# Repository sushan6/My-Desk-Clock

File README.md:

# My Desk Clock

I'm building a custom desk clock using an ESP32. The idea is to make a clock that automatically synchronises its time over Wi-Fi, so there's no need to set the time manually.

I designed the circuit schematic and PCB in KiCad and am also working on a custom 3D-printed enclosure. The clock uses an ESP32 for Wi-Fi connectivity and a dedicated RTC for timekeeping.

## Features

- ESP32-WROOM-32E microcontroller
- Automatic time synchronisation over Wi-Fi using NTP
- DS3231M real-time clock
- Rechargeable battery-based power supply
- USB-C charging and power input
- Custom PCB designed in KiCad
- Five tactile push buttons
- Passive buzzer
- Custom 3D-printed enclosure

# 3D Model

This is the 3D model of the clock enclosure. I designed it around the PCB so that all the components fit inside without making the clock unnecessarily bulky.

# 3D Render

Here's the 3D render of the clock. It gives a better idea of how the finished enclosure is supposed to look.

# Physical PCB Layout

The PCB was designed in KiCad. I arranged the components around the ESP32, RTC, and power management circuit while keeping the board compact enough to fit inside the enclosure.

# Circuit Schematic

The schematic shows how the different sections of the clock connect together, including the ESP32, RTC, battery charging circuit, buck-boost converter, buttons, and buzzer.

# How It Works

The ESP32 is the main controller of the clock. It connects to a Wi-Fi network and retrieves the current time from an NTP server.

The DS3231M RTC provides independent timekeeping, allowing the clock to keep track of time even when Wi-Fi isn't available. The ESP32 can synchronise the RTC when an internet connection is available.

The five tactile buttons are intended for physical controls, while the buzzer can be used for sound alerts.

## Power Management

I designed the power circuit around a rechargeable battery.

- **BQ24074:** Handles battery charging and power management.
- **TPS63031:** Provides regulated power using a buck-boost converter.
- **USB-C connector:** Provides the charging and power input.

The idea is to have a clock that can run without needing to stay connected to a USB cable all the time.

# Design Files

The project includes the KiCad schematic, PCB layout, and 3D enclosure model.

These files can be used to inspect the circuit, modify the PCB, or manufacture your own version of the clock.

# Acknowledgements

This project was designed using **KiCad EDA**. Thanks to the KiCad developers and the open-source hardware community for making PCB design tools accessible.

---

# License

This project is open-source. Feel free to inspect, modify, and build upon the design.

---

# Bill of Materials (BOM)

The following table contains the components used in the clock, along with their quantities, supplier links, and estimated prices.

## Main BOM

| **Item** | **Link** | **Quantity** | **Cost (USD)** | **Notes** |
|---|---|---:|---:|---|
| CR2032 battery holder | [Lion Circuits](https://www.lioncircuits.com/parts/1057) | 1 | $2.11 | Keystone 1057 |
| Passive buzzer | [Robu.in](https://robu.in/product/ac1470-cldz-piezoelectric-passive-buzzer-1-25v14x7mm/) | 1 | $0.09 | 12 × 9.5 mm footprint |
| 100 nF capacitors | [Robu.in](https://robu.in/product/100nf-0805-surface-mount-multilayer-ceramic-capacitor-pack-of-40/) | 3 | $0.03 | 0805 |
| 10 µF capacitors | [Robu.in](https://robu.in/product/0805x106k250nt-fh-25v-10uf-x5r%C2%B110-0805-multilayer-ceramic-capacitors-mlcc-smd-smt-rohs/) | 6 | $0.31 | 0805 |
| 1 µF capacitors | [Robu.in](https://robu.in/product/1uf-1000nf-50v-capacitor-0805-smd-package-pack-of-10/) | 2 | $0.03 | 0805 |
| 4.7 µF capacitor | [Robu.in](https://robu.in/product/20121h475k125ab-tdk-ap-smd-ml-4-7-%c2%b5f-50-v-0805-pack-of-1/) | 1 | $0.15 | 0805 |
| 1×6 pin header | [Robu.in](https://robu.in/product/2-54mm-1x40-pin-male-single-row-straight-short-header-strip-pack-of-3/) | 1 | $0.10 | 2.54 mm |
| 1×4 pin header | [Robu.in](https://robu.in/product/2-54mm-1x40-pin-male-single-row-straight-short-header-strip-pack-of-3/) | 1 | $0.10 | 2.54 mm |
| USB-C receptacle | [Robu.in](https://robu.in/product/u262-161n-4bs165-xkb-5a-1-16p-female-type-c-smd-usb-connectors-rohs/) | 1 | $0.33 | 16-pin |
| JST PH 2-pin connector | [Robu.in](https://robu.in/product/wafer-xh2-54-2pzz-xunpu-1x2p-xh-2p/) | 1 | $0.00 | Verify connector type and price |
| 1.5 µH inductor | [Robu.in](https://robu.in/product/dfe252012p-1r5mp2-murata-power-inductor-smd-1-5-%c2%b5h-shielded-3-a1008-2520-metric/) | 1 | $0.03 | SMD |
| NPN transistor | [Robu.in](https://robu.in/product/s8050-kuu-25v-300mw-500ma-npn-sot-23-bipolar-bjt-rohs/) | 1 | $0.01 | SOT-23 |
| 10 kΩ resistors | [Robu.in](https://robu.in/product/rc0805jr-0710kl-yageo-smd-chip-resistor-10-kohm-pack-of-10/) | 3 | $0.01 | 0805 |
| 4.7 kΩ resistors | [Robu.in](https://robu.in/product/crcw08054k70fkeac-vishay-intertech-4-7k-0805-chip-resistor/) | 3 | $0.02 | 0805 |
| 100 kΩ resistors | [Robu.in](https://robu.in/product/rc0805fr-13100kl-yageo-smd-chip-resistor-100-kohm/) | 2 | $0.02 | 0805 |
| 1 kΩ resistor | [Robu.in](https://robu.in/product/1k-ohm-1-4w-0805-surface-mount-chip-resistor-pack-of-10/) | 1 | $0.00 | 0805 |
| 5.1 kΩ resistors | [Robu.in](https://robu.in/product/era6aeb102vpanasonicsmd-chip-resistor-1-kohm/) | 2 | $0.08 | Verify listing value |
| 1.78 kΩ resistor | [Mouser India](https://www.mouser.in/en/ProductDetail/Panasonic-Industry/ERJ-P06F1781V) | 1 | $0.23 | SMD |
| 3 kΩ resistor | [Robu.in](https://robu.in/product/rc0805fr-073kl-yageo-res-thick-film-0805-3k-ohm/) | 1 | $0.00 | 0805 |
| Tactile push buttons | [Robu.in](https://robu.in/product/6x6x5mm-tactile-push-button-switch-pack-of-20/) | 5 | $0.09 | 6 × 6 mm |
| ESP32-WROOM-32E | [Robu.in](https://robu.in/product/espressif-esp32-wroom-32-4m-32mbit-flash-wifi-bluetooth-module/) | 1 | $3.21 | Main controller |
| DS3231M RTC | [Robu.in](https://robu.in/product/ds3231mtrl-analog-devices-real-time-clock-ic/) | 1 | $3.84 | Real-time clock |
| BQ24074 charger IC | [Robu.in](https://robu.in/product/bq24075rgtt-texas-instruments-vqfn-16-ep3x3-battery-management-rohs/) | 1 | $1.92 | Verify exact part number |
| TPS63031 buck-boost IC | [Robu.in](https://robu.in/product/tps63031dskr-texas-instruments-buck-boost-switching-regulator-ic/) | 1 | $1.90 | Power regulation |

## Cost Summary

| **Item** | **Cost (USD)** |
|---|---:|
| Components | $14.60 |
| PCB | $12.00 |
| **Total estimated cost** | **$26.60** |

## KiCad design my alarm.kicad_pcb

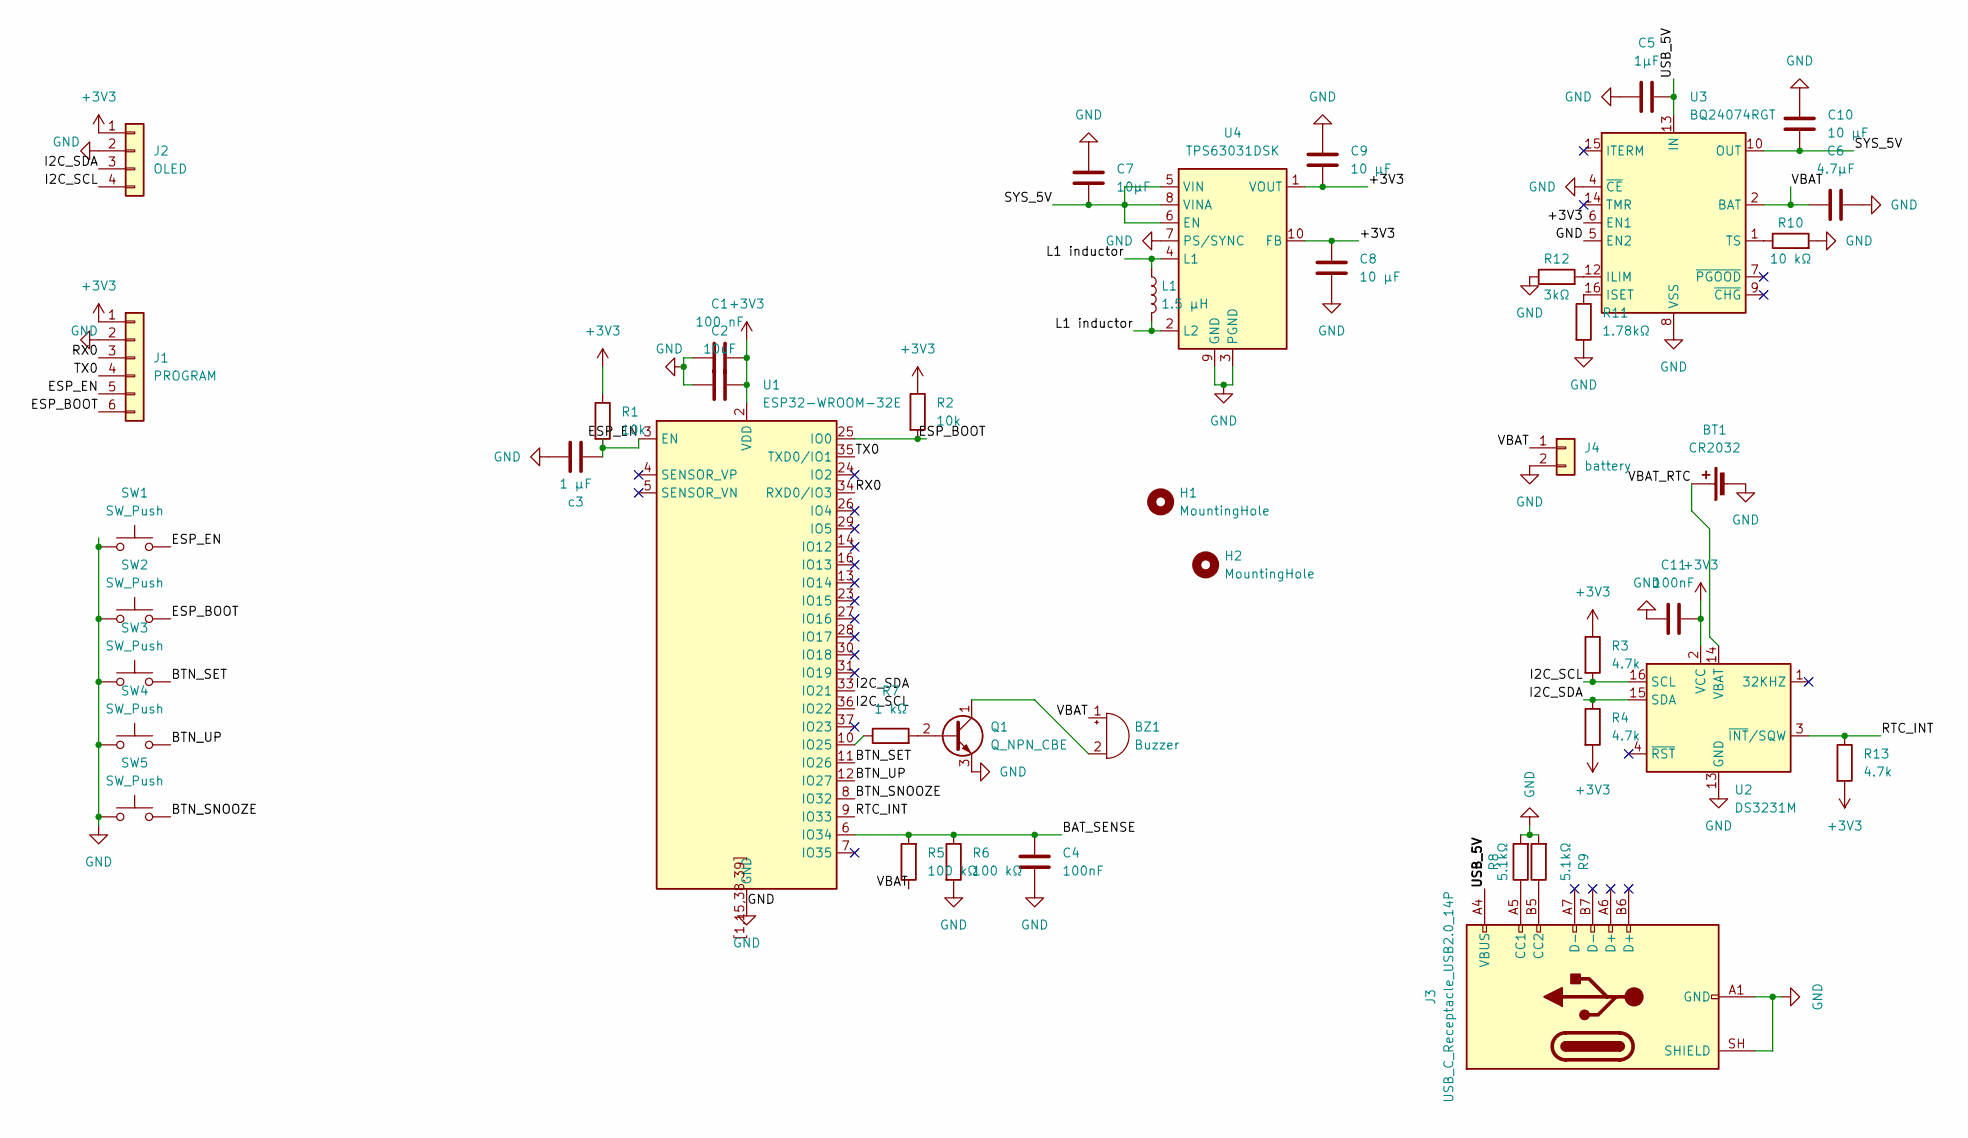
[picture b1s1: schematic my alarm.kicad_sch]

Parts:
BT1: CR2032; BatteryHolder_Keystone_1057_1x2032
BZ1: Buzzer; Buzzer_12x9.5RM7.6
C1: 100 nF; C_0805_2012Metric
C2: 10uF; C_0805_2012Metric
C4, C11: 100nF; C_0805_2012Metric
C5: 1µF; C_0805_2012Metric
C6: 4.7µF; C_0805_2012Metric
C7: 10µF; C_0805_2012Metric
C8, C9, C10: 10 µF; C_0805_2012Metric
H1, H2: MountingHole; MountingHole_2.1mm
J1: PROGRAM; PinHeader_1x06_P2.54mm_Vertical
J2: OLED; PinHeader_1x04_P2.54mm_Vertical
J3: USB_C_Receptacle_USB2.0_14P; USB_C_Receptacle_GCT_USB4105-xx-A_16P_TopMnt_Horizontal
J4: battery; JST_PH_S2B-PH-K_1x02_P2.00mm_Horizontal
L1: 1.5 µH; L_1008_2520Metric_Pad1.43x2.20mm_HandSolder
Q1: Q_NPN_CBE; SOT-23
R1, R2: 10k; R_0805_2012Metric
R3, R4, R13: 4.7k; R_0805_2012Metric
R5, R6: 100 kΩ; R_0805_2012Metric
R7: 1 kΩ; R_0805_2012Metric
R8, R9: 5.1kΩ; R_0805_2012Metric
R10: 10 kΩ; R_0805_2012Metric
R11: 1.78kΩ; R_0805_2012Metric
R12: 3kΩ; R_0805_2012Metric
SW1, SW2, SW3, SW4, SW5: SW_Push; SW_PUSH_6mm
U1: ESP32-WROOM-32E
U2: DS3231M; SOIC-16W_7.5x10.3mm_P1.27mm
U3: BQ24074RGT; VQFN-16-1EP_3x3mm_P0.5mm_EP1.6x1.6mm
U4: TPS63031DSK; WSON-10-1EP_2.5x2.5mm_P0.5mm_EP1.2x2mm
c3: 1 µF; C_0805_2012Metric

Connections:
+3V3: C1.2, C2.2, C8.1, C9.2, C11.1, J1.1, J2.1, R1.1, R2.1, R3.1, R4.2, R13.2, U1.2 (VDD), U2.2 (VCC), U3.6 (EN1), U4.1 (VOUT), U4.10 (FB)
/BAT_SENSE: C4.1, R5.2, R6.1, U1.6 (IO34)
/BTN_SET: SW3.2, U1.11 (IO26)
/BTN_SNOOZE: SW5.2, U1.8 (IO32)
/BTN_UP: SW4.2, U1.12 (IO27)
/ESP_BOOT: J1.6, R2.2, SW2.2, U1.25 (IO0)
/ESP_EN: J1.5, R1.2, SW1.2, U1.3 (EN), c3.2
/I2C_SCL: J2.4, R3.2, U1.36 (IO22), U2.16 (SCL)
/I2C_SDA: J2.3, R4.1, U1.33 (IO21), U2.15 (SDA)
/L1 inductor: L1.1, L1.2, U4.2 (L2), U4.4 (L1)
/RTC_INT: R13.1, U1.9 (IO33), U2.3 (~INT/SQW)
/RX0: J1.3, U1.34 (RXD0/IO3)
/SYS_5V: C7.2, C10.2, U3.10 (OUT), U3.11 (OUT), U4.5 (VIN), U4.6 (EN), U4.8 (VINA)
/TX0: J1.4, U1.35 (TXD0/IO1)
/USB_5V: C5.2, J3.A4 (VBUS), J3.A9 (VBUS), J3.B4 (VBUS), J3.B9 (VBUS), U3.13 (IN)
/VBAT: BZ1.1 (+), C6.1, J4.1, R5.1, U3.2 (BAT), U3.3 (BAT)
/VBAT_RTC: BT1.1 (+), U2.14 (VBAT)
GND: BT1.2 (-), C1.1, C2.1, C4.2, C5.1, C6.2, C7.1, C8.2, C9.1, C10.1, C11.2, J1.2, J2.2, J3.A1 (GND), J3.A12 (GND), J3.B1 (GND), J3.B12 (GND), J3.SH (SHIELD), J4.2, Q1.3 (E), R6.2, R8.2, R9.2, R10.2, R11.2, R12.1, SW1.1, SW2.1, SW3.1, SW4.1, SW5.1, U1.1 (GND), U1.15 (GND), U1.38 (GND), U1.39 (GND), U1.[1,15,38,39] (GND), U2.5 (GND), U2.6 (GND), U2.7 (GND), U2.8 (GND), U2.9 (GND), U2.10 (GND), U2.11 (GND), U2.12 (GND), U2.13 (GND), U3.4 (~CE), U3.5 (EN2), U3.8 (VSS), U3.17 (VSS), U4.3 (PGND), U4.7 (PS/SYNC), U4.9 (GND), U4.11 (PGND), c3.1
unnamed: BZ1.2 (-), Q1.1 (C)
unnamed: J3.A5 (CC1), R8.1
unnamed: J3.B5 (CC2), R9.1
unnamed: Q1.2 (B), R7.2
unnamed: R7.1, U1.10 (IO25)
unnamed: R12.2, U3.12 (ILIM)
unnamed: R11.1, U3.16 (ISET)
unnamed: R10.1, U3.1 (TS)

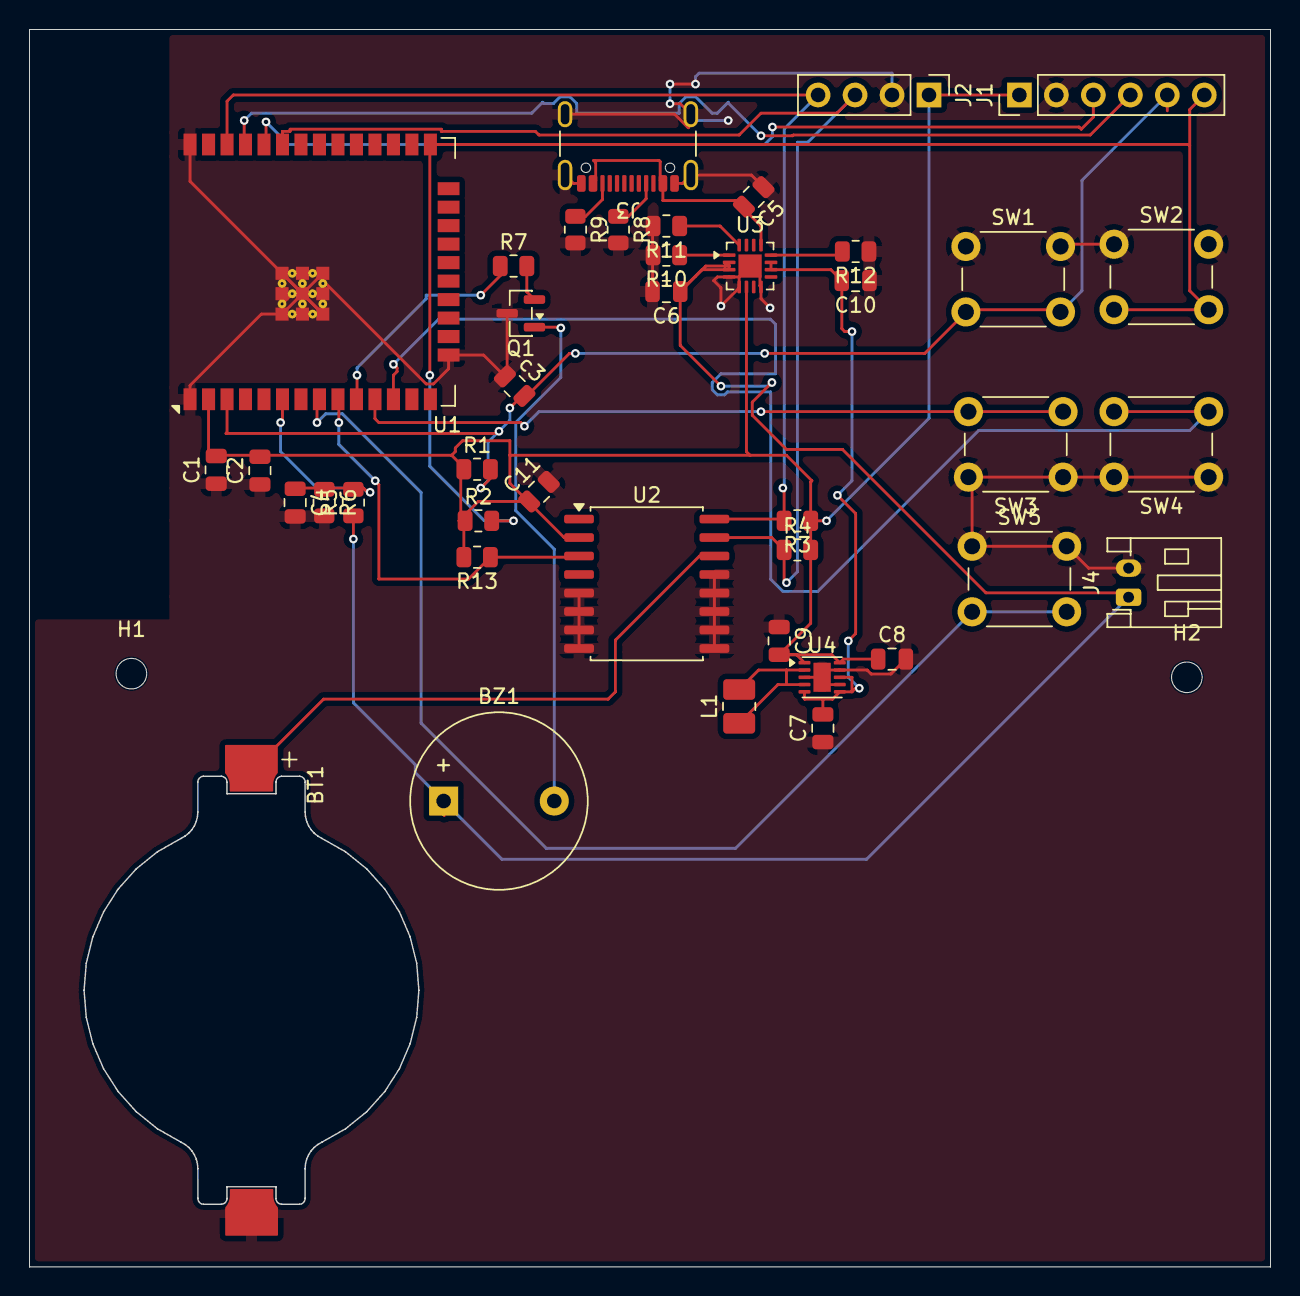
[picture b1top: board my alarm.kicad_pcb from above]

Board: 2 copper layers, 85.2 x 84.9 mm, 43 parts (0 on the bottom side), 26 nets.

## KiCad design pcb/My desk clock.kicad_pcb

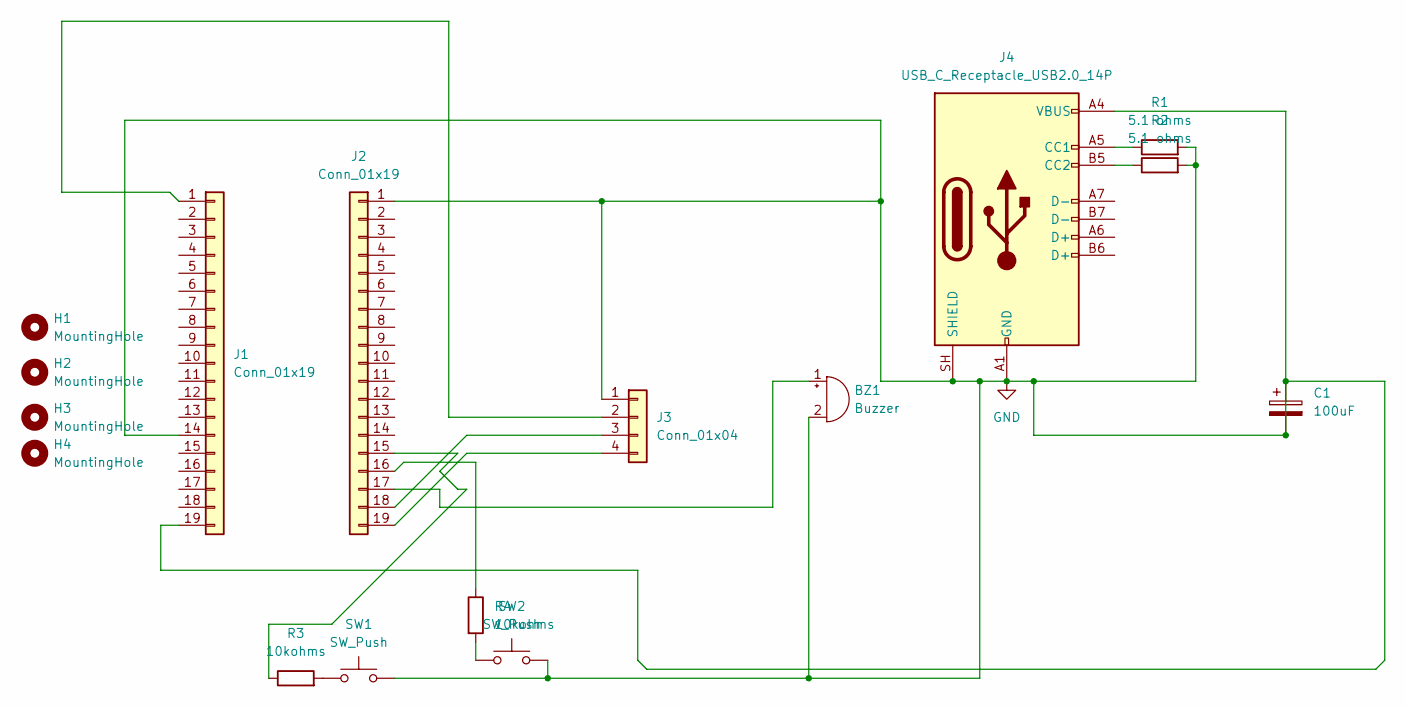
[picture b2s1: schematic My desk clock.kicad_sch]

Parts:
BZ1: Buzzer; Buzzer_Mallory_AST1240MLQ
C1: 100uF; DX_5R5VxxxxU_D11.5mm_P5.00mm
H1, H2, H3, H4: MountingHole; MountingHole_3.2mm_M3
J1, J2: Conn_01x19; PinSocket_1x19_P2.54mm_Vertical
J3: Conn_01x04; PinSocket_1x04_P2.54mm_Vertical
J4: USB_C_Receptacle_USB2.0_14P; USB_C_Receptacle_HRO_TYPE-C-31-M-12
R1, R2: 5.1 ohms; R_0805_2012Metric
R3, R4: 10kohms; R_0805_2012Metric
SW1, SW2: SW_Push; SW_PUSH_6mm

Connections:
GND: BZ1.2 (-), C1.1, C1.2, J1.14, J1.19, J2.1, J3.1, J4.A1 (GND), J4.A4 (VBUS), J4.A9 (VBUS), J4.A12 (GND), J4.B1 (GND), J4.B4 (VBUS), J4.B9 (VBUS), J4.B12 (GND), J4.SH (SHIELD), R1.2, R2.2, SW1.2, SW2.2
unnamed: BZ1.1 (+), J2.17
unnamed: J1.1, J3.2
unnamed: J2.15, R3.1
unnamed: J2.16, R4.1
unnamed: J2.18, J3.3
unnamed: J2.19, J3.4
unnamed: J4.A5 (CC1), R1.1
unnamed: J4.B5 (CC2), R2.1
unnamed: R3.2, SW1.1
unnamed: R4.2, SW2.1

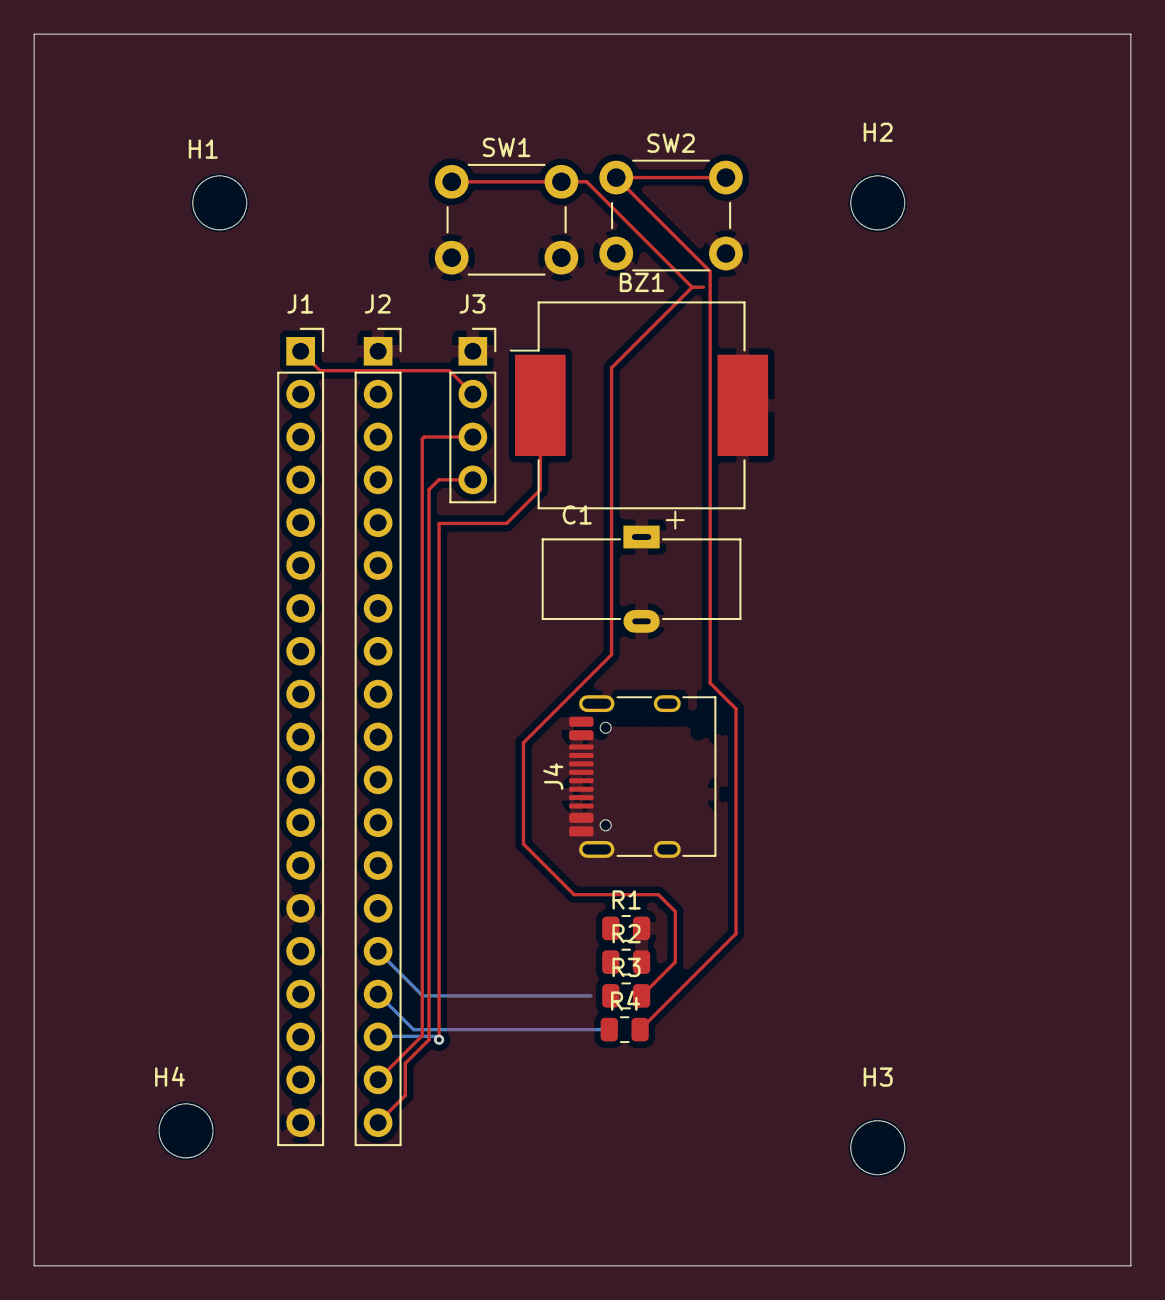
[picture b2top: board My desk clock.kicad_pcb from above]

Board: 2 copper layers, 65.0 x 73.0 mm, 16 parts (0 on the bottom side), 11 nets.

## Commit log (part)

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2026-06-01 Initial setup of my desk clock project files
2026-06-01 Added initial PCB layout design
2026-06-01 Generated first 3D render of the board layout
2026-06-01 Finalized PCB layout and added production-ready Gerber manufacturing files
2026-06-01 Update README with 3D render and schematic images
    Added sections for 3D render, PCB layout, and circuit schematic with images.
2026-06-01 Added bold titles for schematic and PCB image sections
2026-06-01 Add 3D printable enclosure STL models to repository
2026-06-01 Add 3D model section to README
